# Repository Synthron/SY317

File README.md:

# Switching Power Supply Modules

## SY317
78xx compatible Switching Regulator

 - Input Voltage: 4.5V .. 24V
 - Output Voltage: 1.1V .. 16V
 - Output Current: 3A
 - Switching Frequency: 500kHz
 - Efficiency: 85-95% 
 - Output Ripple: <50mV

pincompatible to the popular 78xx series linear voltage regulators

Very small form factor at 10x25mm dimensions

## CB350
High current Switching Regulator

- 12..24V Input
- 5V2, 6V2, 7V4 and 8V4 fixed output
  - use solder bridge to select output voltage
  - different resistor values for voltages given in schematic
- 12A of current!

Intended for Servo Control, featuring 4 Pin-Headers for Servo control

features pin header for additional SY317 module for an additional variable 3A output voltage

compact form factor at 25x50mm dimensions

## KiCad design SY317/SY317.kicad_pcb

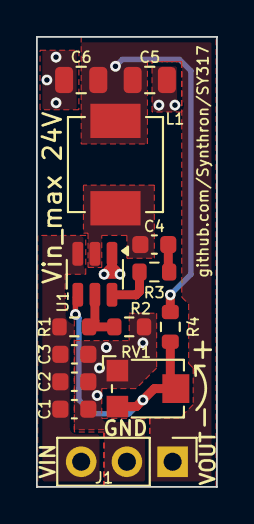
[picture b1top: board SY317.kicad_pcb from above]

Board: 2 copper layers, 10.0 x 25.0 mm, 14 parts (0 on the bottom side), 8 nets.

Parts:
C1, C2: 10µ; C_0603_1608Metric
C3, C4: 100n; C_0603_1608Metric
C5, C6: 22µ; C_0805_2012Metric
J1: Conn_01x03; PinHeader_1x03_P2.54mm_Vertical
L1: 5µ6H; L_Vishay_IHLP-2020
R1: 180k; R_0603_1608Metric
R2: 39k; R_0603_1608Metric
R3: 30; R_0603_1608Metric
R4: 22k; R_0603_1608Metric
RV1: 50k; Potentiometer_Bourns_TC33X_Vertical
U1: TPS56339DDC; SOT-23-6

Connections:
GND: C1.2, C2.2, C3.2, C5.2, C6.2, J1.2, R2.2, RV1.1, U1.1 (GND)
unnamed: C4.1, R3.1
unnamed: R3.2, U1.6 (BOOT)
unnamed: R1.2, R2.1, U1.5 (EN)
unnamed: R4.2, RV1.2, RV1.3, U1.4 (FB)
unnamed: C4.2, L1.1, U1.2 (SW)
VD: C1.1, C2.1, C3.1, J1.3, R1.1, U1.3 (VIN)
VDD: C5.1, C6.1, J1.1, L1.2, R4.1

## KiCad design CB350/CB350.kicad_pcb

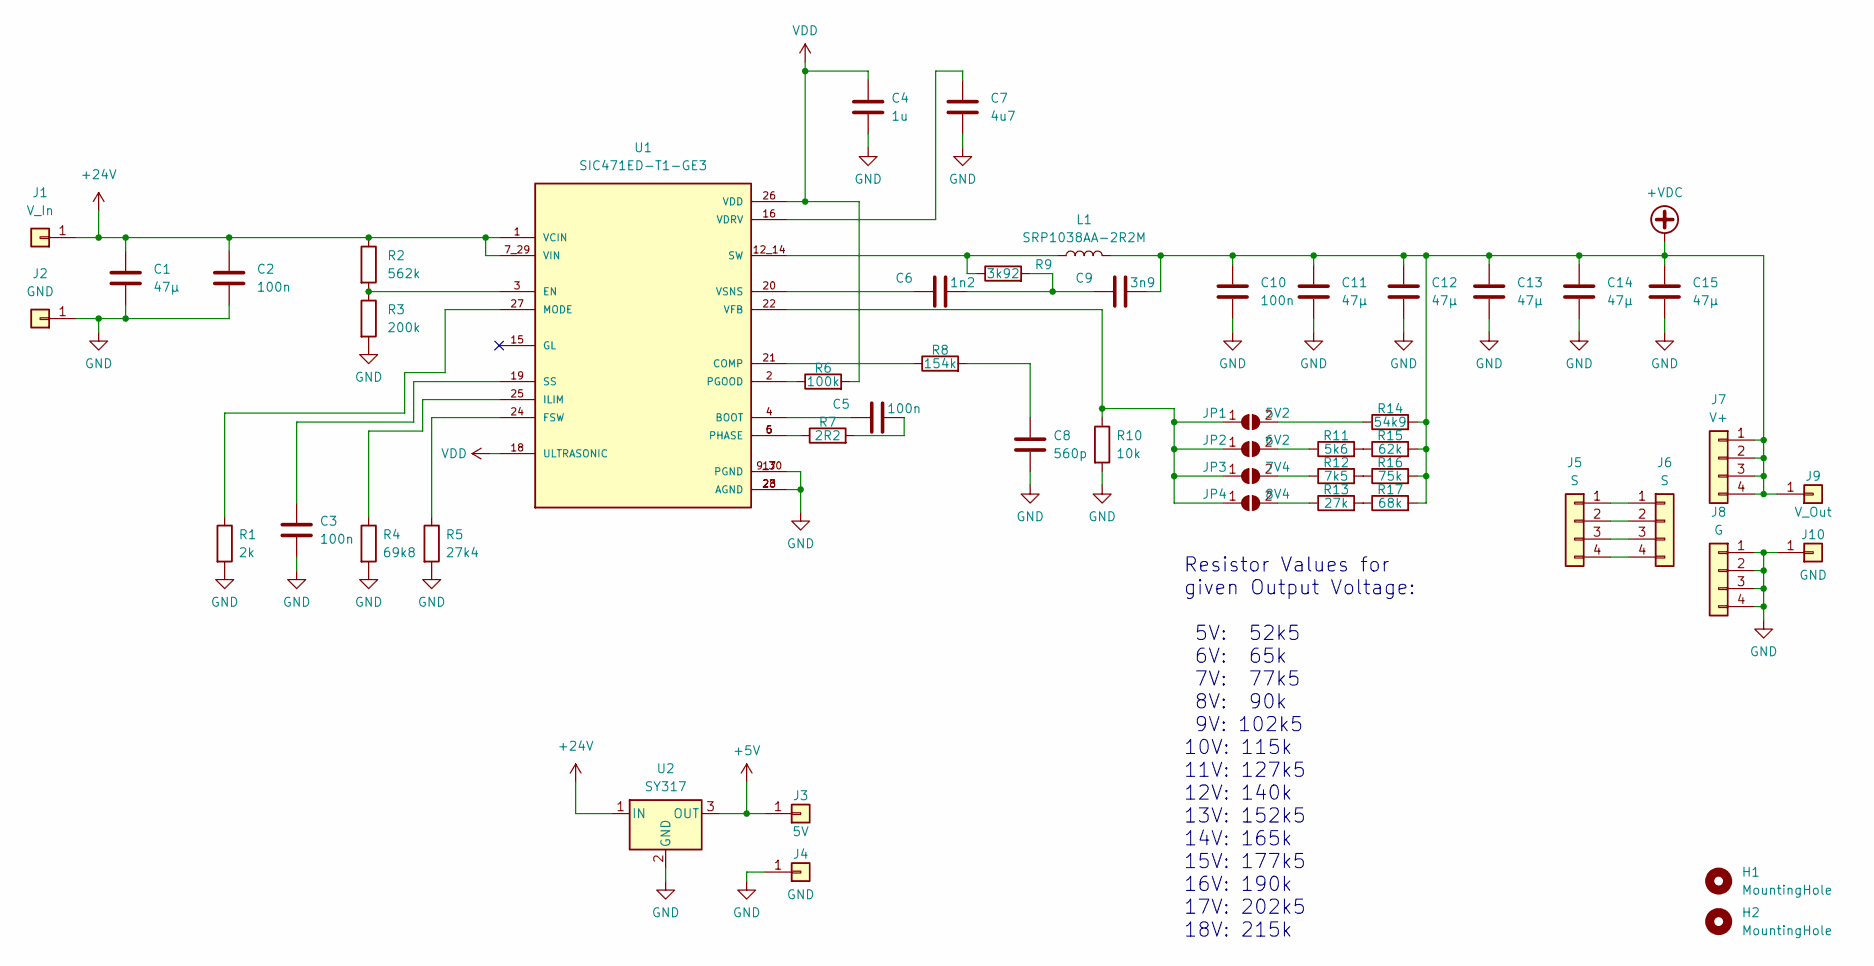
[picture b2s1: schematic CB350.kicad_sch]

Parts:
C1, C11, C12, C13, C14, C15: 47µ; C_1210_3225Metric
C2, C3, C5, C10: 100n; C_0603_1608Metric
C4: 1u; C_0603_1608Metric
C6: 1n2; C_0603_1608Metric
C7: 4u7; C_0603_1608Metric
C8: 560p; C_0603_1608Metric
C9: 3n9; C_0603_1608Metric
H1, H2: MountingHole; MountingHole_3.2mm_M3_DIN965
J1: V_In; TestPoint_THTPad_4.0x4.0mm_Drill2.0mm
J2, J10: GND; TestPoint_THTPad_4.0x4.0mm_Drill2.0mm
J3: 5V; TestPoint_THTPad_2.5x2.5mm_Drill1.2mm
J4: GND; TestPoint_THTPad_2.5x2.5mm_Drill1.2mm
J5, J6: S; PinHeader_1x04_P2.54mm_Vertical
J7: V+; PinHeader_1x04_P2.54mm_Vertical
J8: G; PinHeader_1x04_P2.54mm_Vertical
J9: V_Out; TestPoint_THTPad_4.0x4.0mm_Drill2.0mm
JP1: 5V2; SolderJumper-2_P1.3mm_Open_TrianglePad1.0x1.5mm
JP2: 6V2; SolderJumper-2_P1.3mm_Open_TrianglePad1.0x1.5mm
JP3: 7V4; SolderJumper-2_P1.3mm_Open_TrianglePad1.0x1.5mm
JP4: 8V4; SolderJumper-2_P1.3mm_Open_TrianglePad1.0x1.5mm
L1: SRP1038AA-2R2M; L_Bourns_SRP1038C_10.0x10.0mm
R1: 2k; R_0603_1608Metric
R2: 562k; R_0603_1608Metric
R3: 200k; R_0603_1608Metric
R4: 69k8; R_0603_1608Metric
R5: 27k4; R_0603_1608Metric
R6: 100k; R_0603_1608Metric
R7: 2R2; R_0603_1608Metric
R8: 154k; R_0603_1608Metric
R9: 3k92; R_0603_1608Metric
R10: 10k; R_0603_1608Metric
R11: 5k6; R_0603_1608Metric
R12: 7k5; R_0603_1608Metric
R13: 27k; R_0603_1608Metric
R14: 54k9; R_0603_1608Metric
R15: 62k; R_0603_1608Metric
R16: 75k; R_0603_1608Metric
R17: 68k; R_0603_1608Metric
U1: SIC471ED-T1-GE3; VREG_SIC471ED-T1-GE3; PARTREV D
U2: SY317; TO-220-3_Vertical

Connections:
+5V: J3.1, U2.3 (OUT)
+24V: C1.1, C2.1, J1.1, R2.1, U1.1 (VCIN), U1.7_29 (VIN), U2.1 (IN)
+VDC: C9.2, C10.1, C11.1, C12.1, C13.1, C14.1, C15.1, J7.1, J7.2, J7.3, J7.4, J9.1, L1.2, R14.2, R15.2, R16.2, R17.2
GND: C1.2, C2.2, C3.2, C4.2, C7.2, C8.2, C10.2, C11.2, C12.2, C13.2, C14.2, C15.2, J2.1, J4.1, J8.1, J8.2, J8.3, J8.4, J10.1, R1.2, R3.2, R4.2, R5.2, R10.2, U1.9_30 (PGND), U1.17 (PGND), U1.23 (AGND), U1.28 (AGND), U2.2 (GND)
unnamed: C5.2, R7.2
unnamed: C6.2, C9.1, R9.2
unnamed: C8.1, R8.2
unnamed: J5.1, J6.1
unnamed: J5.2, J6.2
unnamed: J5.3, J6.3
unnamed: J5.4, J6.4
unnamed: JP1.1 (A), JP2.1 (A), JP3.1 (A), JP4.1 (A), R10.1, U1.22 (VFB)
unnamed: JP1.2 (B), R14.1
unnamed: JP2.2 (B), R11.1
unnamed: JP3.2 (B), R12.1
unnamed: JP4.2 (B), R13.1
unnamed: R7.1, U1.5 (PHASE), U1.6 (PHASE)
unnamed: R11.2, R15.1
unnamed: R12.2, R16.1
unnamed: R13.2, R17.1
unnamed: C5.1, U1.4 (BOOT)
unnamed: R8.1, U1.21 (COMP)
unnamed: R2.2, R3.1, U1.3 (EN)
unnamed: R5.1, U1.24 (FSW)
unnamed: R4.1, U1.25 (ILIM)
unnamed: R1.1, U1.27 (MODE)
unnamed: R6.1, U1.2 (PGOOD)
unnamed: C3.1, U1.19 (SS)
unnamed: L1.1, R9.1, U1.12_14 (SW)
unnamed: C7.1, U1.16 (VDRV)
unnamed: C6.1, U1.20 (VSNS)
VDD: C4.1, R6.2, U1.18 (ULTRASONIC), U1.26 (VDD)

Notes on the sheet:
Resistor Values for given Output Voltage: 5V: 52k5 6V: 65k 7V: 77k5 8V: 90k 9V: 102k5 10V: 115k 11V: 127k5 12V: 140k 13V: 152k5 14V: 165k 15V: 177k5 16V: 190k 17V: 202k5 18V: 215k

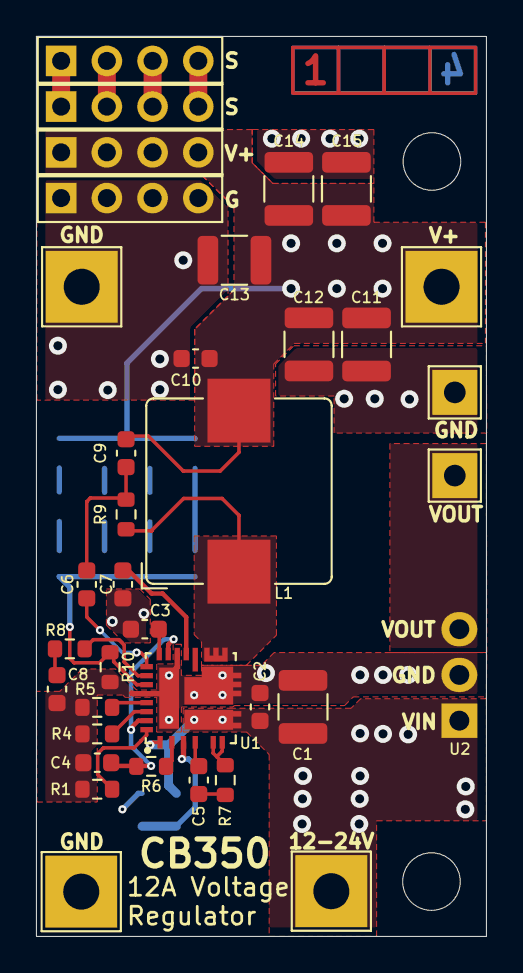
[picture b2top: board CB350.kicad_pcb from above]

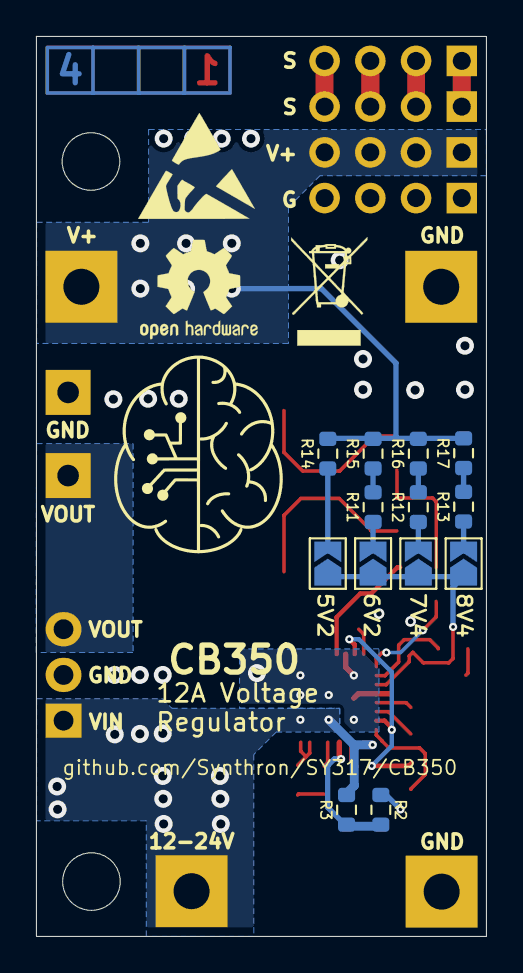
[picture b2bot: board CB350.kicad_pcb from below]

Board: 4 copper layers, 25.0 x 50.0 mm, 51 parts (13 on the bottom side), 32 nets.

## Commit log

2024-04-11 silkscreen fix
2024-04-17 new module and readme update
2024-04-18 Update CB350 files, cleanup repo
2024-05-04 Overhaul
